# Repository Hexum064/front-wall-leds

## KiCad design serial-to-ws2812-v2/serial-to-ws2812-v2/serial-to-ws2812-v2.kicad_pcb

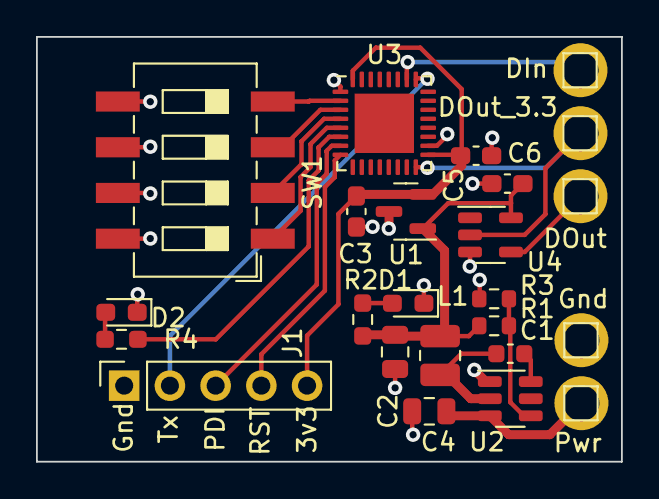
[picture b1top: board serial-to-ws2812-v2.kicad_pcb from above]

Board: 2 copper layers, 32.5 x 23.6 mm, 24 parts (0 on the bottom side), 20 nets.

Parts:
C1: 0.1uF; C_0603_1608Metric
C2, C4: 22uF; C_0805_2012Metric
C3: 22uF; C_0603_1608Metric_Pad1.08x0.95mm_HandSolder
C5, C6: 0.1uF; C_0603_1608Metric_Pad1.08x0.95mm_HandSolder
D1, D2: LED_Small; LED_0603_1608Metric_Pad1.05x0.95mm_HandSolder
DIn: DIn; Pin_D0.7mm_L6.5mm_W1.8mm_FlatFork
DOut: DOut_5v; Pin_D0.7mm_L6.5mm_W1.8mm_FlatFork
DOut_3.3: DOut; Pin_D0.7mm_L6.5mm_W1.8mm_FlatFork
Gnd: Gnd; Pin_D0.7mm_L6.5mm_W1.8mm_FlatFork
J1: PRG_DEBUG; PinSocket_1x05_P2.54mm_Vertical
L1: 3.3uH; L_1008_2520Metric
Pwr: Pwr; Pin_D0.7mm_L6.5mm_W1.8mm_FlatFork
R1: 56.2k; R_0603_1608Metric
R2, R4: 1k; R_0603_1608Metric_Pad0.98x0.95mm_HandSolder
R3: 10k; R_0603_1608Metric
SW1: SW_DIP_x04; SW_DIP_SPSTx04_Slide_6.7x11.72mm_W8.61mm_P2.54mm_LowProfile
U1: AP7333-33SAG-7; SOT-23
U2: AP62300; TSOT-23-6
U3: ATxmega32E5-A; QFN-32-1EP_5x5mm_P0.5mm_EP3.3x3.3mm
U4: SN74LV1T34DBV; SOT-23-5

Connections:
+3V3: C3.1, C5.1, J1.5, U1.2 (VO), U3.17 (VCC), U3.32 (AVCC)
+5V: C2.1, C6.1, L1.2, R1.1, R2.1, U1.1 (VI), U4.5 (VCC)
GND: C2.2, C3.2, C4.2, C5.2, C6.2, D1.1 (K), D2.1 (K), Gnd.1, J1.1, R3.2, SW1.5, SW1.6, SW1.7, SW1.8, U1.3 (GND), U2.1 (GND), U3.1 (GND), U3.18 (GND), U4.3 (GND)
unnamed: C1.1, L1.1, U2.2 (SW)
unnamed: C1.2, U2.6 (BST)
unnamed: D1.2 (A), R2.2
unnamed: D2.2 (A), R4.1
unnamed: J1.2, U3.25 (PD3)
unnamed: J1.3, U3.7 (PDI_DATA)
unnamed: J1.4, U3.8 (~RESET/PDI_CLK)
unnamed: DOut_3.3.1, U3.16 (PC0), U4.2 (A)
unnamed: DIn.1, U3.26 (PD2)
unnamed: DOut.1, U4.4 (Y)
unnamed: R1.2, R3.1, U2.4 (FB)
unnamed: R4.2, U3.6 (AREF/PA0)
unnamed: SW1.1, U3.5 (PA1)
unnamed: SW1.2, U3.4 (PA2)
unnamed: SW1.3, U3.3 (PA3)
unnamed: SW1.4, U3.2 (PA4)
VCC: C4.1, Pwr.1, U2.3 (VIN)

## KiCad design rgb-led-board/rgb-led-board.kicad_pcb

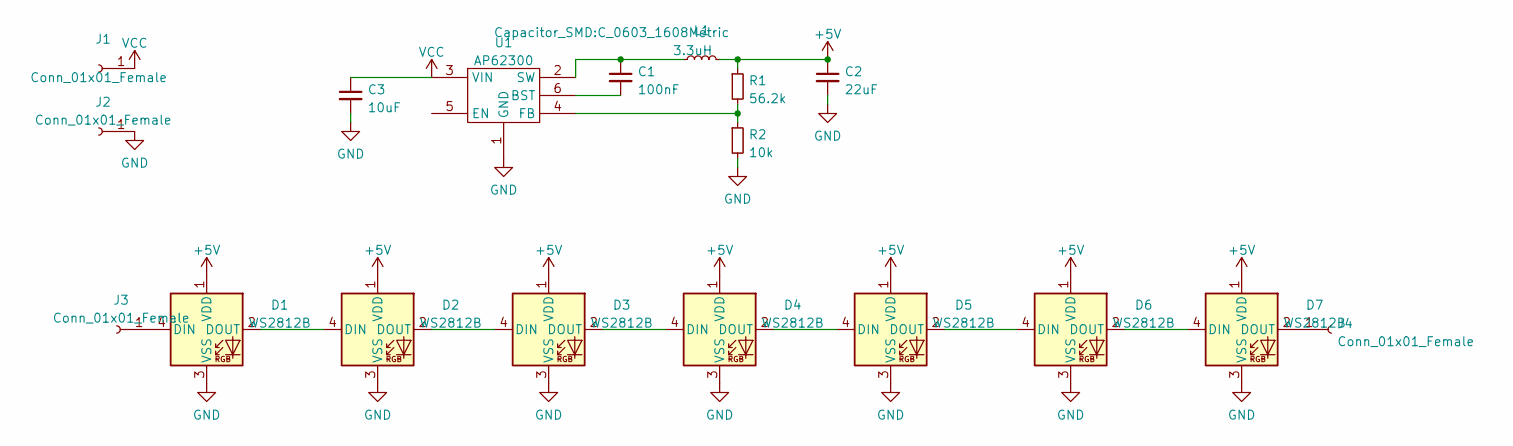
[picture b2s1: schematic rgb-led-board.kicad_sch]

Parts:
C1: 100nF; C_0603_1608Metric
C2: 22uF; C_0805_2012Metric
C3: 10uF; C_0805_2012Metric
D1, D2, D3, D4, D5, D6, D7: WS2812B; LED_WS2812B_PLCC4_5.0x5.0mm_P3.2mm
J1, J2, J3, J4: Conn_01x01_Female; TestPoint_Plated_Hole_D2.0mm
L1: 3.3uH; L_1008_2520Metric
R1: 56.2k; R_0603_1608Metric
R2: 10k; R_0603_1608Metric
U1: AP62300; TSOT-23-6

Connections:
+5V: C2.1, D1.1 (VDD), D2.1 (VDD), D3.1 (VDD), D4.1 (VDD), D5.1 (VDD), D6.1 (VDD), D7.1 (VDD), L1.2, R1.1
GND: C2.2, C3.2, D1.3 (VSS), D2.3 (VSS), D3.3 (VSS), D4.3 (VSS), D5.3 (VSS), D6.3 (VSS), D7.3 (VSS), J2.1, R2.2, U1.1 (GND)
unnamed: C1.1, L1.1, U1.2 (SW)
unnamed: C1.2, U1.6 (BST)
unnamed: D1.2 (DOUT), D2.4 (DIN)
unnamed: D1.4 (DIN), J3.1
unnamed: D2.2 (DOUT), D3.4 (DIN)
unnamed: D3.2 (DOUT), D4.4 (DIN)
unnamed: D4.2 (DOUT), D5.4 (DIN)
unnamed: D5.2 (DOUT), D6.4 (DIN)
unnamed: D6.2 (DOUT), D7.4 (DIN)
unnamed: D7.2 (DOUT), J4.1
unnamed: R1.2, R2.1, U1.4 (FB)
VCC: C3.1, J1.1, U1.3 (VIN)

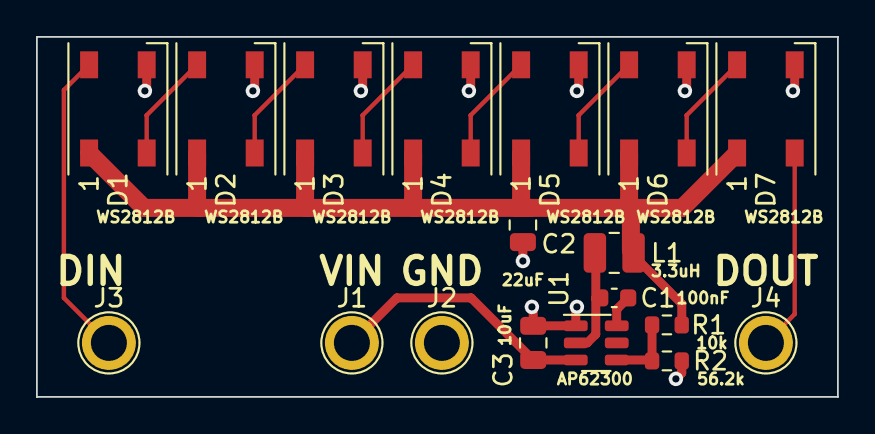
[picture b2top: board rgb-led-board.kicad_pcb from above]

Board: 2 copper layers, 44.5 x 20.0 mm, 18 parts (0 on the bottom side), 14 nets.

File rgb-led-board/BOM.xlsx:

Comment | Designator | Footprint | JLCPCB Part #（optional）
AP62300 | U1 | TSOT-23-6 | C1883519
3.3uH | L1 | 1008 | C161085
100nF | C1 | 0603 | C1590
22uF | C2 | 0805 | C602037
10uF | C3 | 0805 | C84416
56.2K Ohm | R1 | 0603 | C168337
10k Ohm | R2 | 0603 | C103210
WS2812B | D1,D2,D3,D4,D5,D6,D7 | LED_WS2812B_PLCC4_5.0x5.0mm_P3.2mm | C2920042

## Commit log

2023-04-20 init commit
2023-07-13 moved test-driver
2024-07-04 update naming
2024-07-04 renaming folder
